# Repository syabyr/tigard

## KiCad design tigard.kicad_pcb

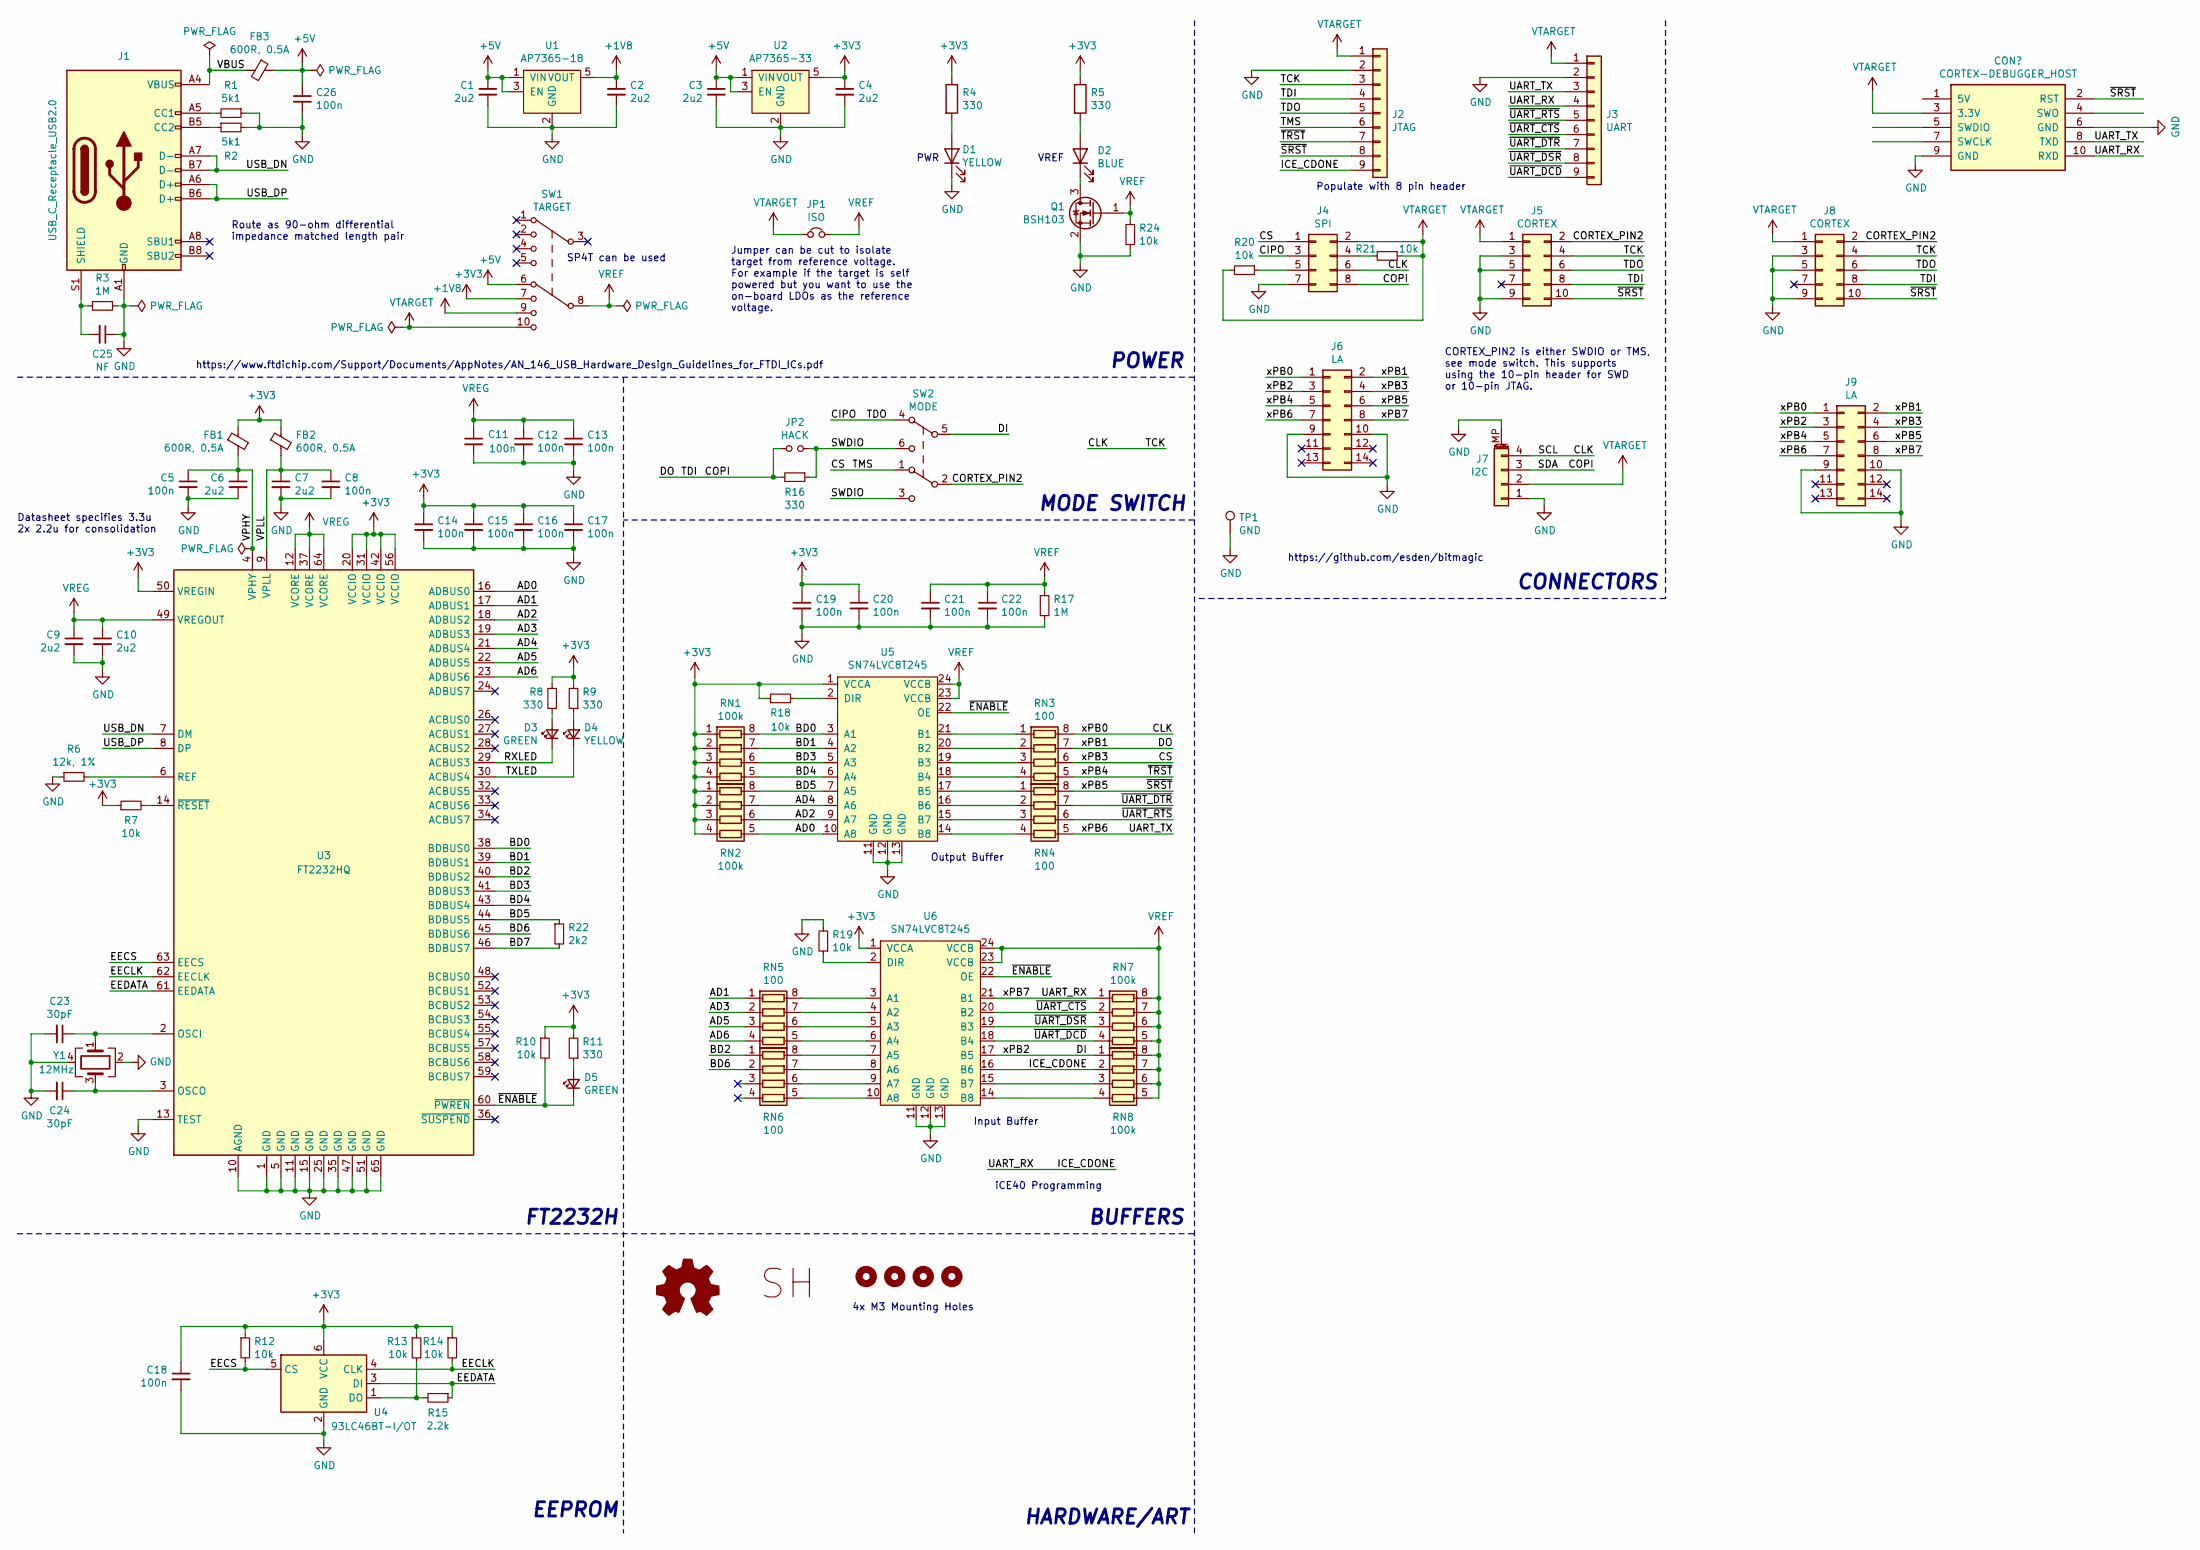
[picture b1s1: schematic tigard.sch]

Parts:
C1, C2, C3, C4, C6, C7, C9, C10: 2u2; C_0402_1005Metric; LCSC C307419
C5, C8, C11, C12, C13, C14, C15, C16, C17, C18, C19, C20, C21, C22, C26: 100n; C_0402_1005Metric; LCSC C100072
C23, C24: 30pF; C_0402_1005Metric; LCSC C159804
C25: NF; C_0402_1005Metric
D1, D4: YELLOW; LED_0603_1608Metric; LCSC C160477
D2: BLUE; LED_0603_1608Metric; LCSC C157738
D3, D5: GREEN; LED_0603_1608Metric; LCSC C12065
FB1, FB2, FB3: 600R, 0.5A; L_0402_1005Metric; LCSC C76886
H1, H2, H3, H4: MountingHole; MountingHole_3.2mm_M3_ISO7380
J1: USB_C_Receptacle_USB2.0; USB_C_Receptacle_HRO_TYPE-C-31-M-12; LCSC C165948
J2: JTAG; PinHeader_1x09_P2.54mm_Vertical; LCSC C358689
J3: UART; PinHeader_1x09_P2.54mm_Vertical; LCSC C492408
J4: SPI; PinHeader_2x04_P2.54mm_Vertical; LCSC C358693
J5: CORTEX; PinHeader_2x05_P1.27mm_Vertical_SMD; LCSC C448647
J6: LA; PinHeader_2x07_P1.27mm_Vertical_SMD
J7: I2C; JST_SH_SM04B-SRSS-TB_1x04-1MP_P1.00mm_Horizontal; LCSC C160404
J8: CORTEX; debugger_2x05_P1.27mm_Vertical; LCSC C448647
J9: LA; PinHeader_2x07_P1.27mm_Vertical
JP1: ISO; SolderJumper-2_P1.3mm_Bridged_RoundedPad1.0x1.5mm
JP2: HACK; SolderJumper-2_P1.3mm_Open_RoundedPad1.0x1.5mm
LOGO1: Logo_Open_Hardware_Small; OSHW-Symbol_4.4x4mm_SilkScreen
LOGO2: Logo_SH; Securing_Hardware_Logo
Q1: BSH103; SOT-23_RoundRect; LCSC C88711
R1, R2: 5k1; R_0402_1005Metric; LCSC C25941
R3, R17: 1M; R_0402_1005Metric; LCSC C26087
R4, R5, R8, R9, R11, R16: 330; R_0402_1005Metric; LCSC C25104
R6: 12k, 1%; R_0402_1005Metric; LCSC C25752
R7, R10, R12, R13, R14, R18, R19, R20, R21, R24: 10k; R_0402_1005Metric; LCSC C301923
R15: 2.2k; R_0402_1005Metric; LCSC C25879
R22: 2k2; R_0402_1005Metric; LCSC C25933
RN1, RN2, RN7, RN8: 100k; R_Array_Convex_4x0402_RoundRect; LCSC C25724
RN3, RN4, RN5, RN6: 100; R_Array_Convex_4x0402_RoundRect; LCSC C48442
SW1: TARGET; SW_ALPS_SSSS224100_DP4T; LCSC C255514
SW2: MODE; SW_CuK_JS202011CQN_DPDT_Straight; LCSC C221663
TP1: GND; TestPoint_Keystone_5000-5004_Miniature; LCSC C238122
U1: AP7365-18; SOT-23-5_RoundRect; LCSC C460402
U2: AP7365-33; SOT-23-5_RoundRect; LCSC C150742
U3: FT2232HQ; QFN-64-1EP_9x9mm_P0.5mm_EP4.35x4.35mm_ThermalVias; LCSC C193662
U4: 93LC46BT-I/OT; SOT-23-6_RoundRect; LCSC C190271
U5, U6: SN74LVC8T245; TSSOP-24_4.4x7.8mm_P0.65mm; LCSC C27643
Y1: 12MHz; Crystal_SMD_3225-4Pin_3.2x2.5mm_RoundRect; LCSC C9002

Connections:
+1V8: C2.1, SW1.9, U1.5 (VOUT)
+3V3: C4.1, C14.1, C15.1, C16.1, C17.1, C18.1, C19.1, C20.1, FB1.1, FB2.1, R4.1, R5.1, R7.1, R8.2, R9.2, R10.1, R11.2, R12.1, R13.1, R14.1, R18.1, RN1.1 (R1.1), RN1.2 (R2.1), RN1.3 (R3.1), RN1.4 (R4.1), RN2.1 (R1.1), RN2.2 (R2.1), RN2.3 (R3.1), RN2.4 (R4.1), SW1.7, U2.5 (VOUT), U3.20 (VCCIO), U3.31 (VCCIO), U3.42 (VCCIO), U3.50 (VREGIN), U3.56 (VCCIO), U4.6 (VCC), U5.1 (VCCA), U6.1 (VCCA)
+5V: C1.1, C3.1, C26.1, FB3.1, SW1.6, U1.1 (VIN), U1.3 (EN), U2.1 (VIN), U2.3 (EN)
/AD0: RN2.5 (R4.2), U3.16 (ADBUS0), U5.10 (A8)
/AD1: RN5.1 (R1.1), U3.17 (ADBUS1)
/AD2: RN2.6 (R3.2), U3.18 (ADBUS2), U5.9 (A7)
/AD3: RN5.2 (R2.1), U3.19 (ADBUS3)
/AD4: RN2.7 (R2.2), U3.21 (ADBUS4), U5.8 (A6)
/AD5: RN5.3 (R3.1), U3.22 (ADBUS5)
/AD6: RN5.4 (R4.1), U3.23 (ADBUS6)
/BD0: RN1.8 (R1.2), U3.38 (BDBUS0), U5.3 (A1)
/BD1: RN1.7 (R2.2), U3.39 (BDBUS1), U5.4 (A2)
/BD2: RN6.1 (R1.1), U3.40 (BDBUS2)
/BD3: RN1.6 (R3.2), U3.41 (BDBUS3), U5.5 (A3)
/BD4: RN1.5 (R4.2), U3.43 (BDBUS4), U5.6 (A4)
/BD5: R22.1, RN2.8 (R1.2), U3.44 (BDBUS5), U5.7 (A5)
/BD6: RN6.2 (R2.1), U3.45 (BDBUS6)
/BD7: R22.2, U3.46 (BDBUS7)
/CIPO: J2.5, J4.3, J5.6, J8.6, SW2.4
/CLK: J2.3, J4.6, J5.4, J6.1, J7.4, J8.4, J9.1, RN3.8 (R1.2)
/COPI: J2.4, J4.8, J5.8, J6.2, J7.3, J8.8, J9.2, JP2.1, R16.2, RN3.7 (R2.2)
/CORTEX_PIN2: J5.2, J8.2, SW2.2
/CS: J2.6, J4.1, J6.4, J9.4, RN3.6 (R3.2), SW2.1
/DI: J6.3, J9.3, RN8.1 (R1.1), SW2.5, U6.17 (B5)
/EECLK: R14.2, U3.62 (EECLK), U4.4 (CLK)
/EECS: R12.2, U3.63 (EECS), U4.5 (CS)
/EEDATA: R15.1, U3.61 (EEDATA), U4.3 (DI)
/ICE_CDONE: J2.9, J3.4, J6.8, J9.8, RN7.1 (R1.1), RN8.2 (R2.1), U6.16 (B6), U6.21 (B1)
/RXLED: D3.1 (K), U3.29 (ACBUS3)
/SWDIO: JP2.2, R16.1, SW2.3, SW2.6
/TXLED: D4.1 (K), U3.30 (ACBUS4)
/UART_TX: J3.3, J6.7, J9.7, RN4.5 (R4.2)
/USB_DN: J1.A7 (D-), J1.B7 (D-), U3.7 (DM)
/USB_DP: J1.A6 (D+), J1.B6 (D+), U3.8 (DP)
/VBUS: FB3.2, J1.A4 (VBUS), J1.A9 (VBUS), J1.B4 (VBUS), J1.B9 (VBUS)
/VPHY: C5.1, C6.1, FB1.2, U3.4 (VPHY)
/VPLL: C7.1, C8.1, FB2.2, U3.9 (VPLL)
/xPB4: J2.7, J6.5, J9.5, RN3.5 (R4.2)
/xPB5: J2.8, J5.10, J6.6, J8.10, J9.6, RN4.8 (R1.2)
/~ENABLE: D5.1 (K), R10.2, U3.60 (~PWREN), U5.22 (OE), U6.22 (OE)
/~UART_CTS: J3.6, RN7.2 (R2.1), U6.20 (B2)
/~UART_DCD: J3.9, RN7.4 (R4.1), U6.18 (B4)
/~UART_DSR: J3.8, RN7.3 (R3.1), U6.19 (B3)
/~UART_DTR: J3.7, RN4.7 (R2.2)
/~UART_RTS: J3.5, RN4.6 (R3.2)
GND: C1.2, C2.2, C3.2, C4.2, C5.2, C6.2, C7.2, C8.2, C9.2, C10.2, C11.2, C12.2, C13.2, C14.2, C15.2, C16.2, C17.2, C18.2, C19.2, C20.2, C21.2, C22.2, C23.2, C24.2, C25.1, C26.2, D1.1 (K), J1.A1 (GND), J1.A12 (GND), J1.B1 (GND), J1.B12 (GND), J2.2, J3.2, J4.7, J5.3, J5.5, J5.9, J6.9, J6.10, J7.1, J7.MP (MountPin), J8.3, J8.5, J8.9, J9.9, J9.10, Q1.2 (S), R1.1, R2.2, R3.1, R6.1, R17.2, R19.2, R24.1, TP1.1, U1.2 (GND), U2.2 (GND), U3.1 (GND), U3.5 (GND), U3.10 (AGND), U3.11 (GND), U3.13 (TEST), U3.15 (GND), U3.25 (GND), U3.35 (GND), U3.47 (GND), U3.51 (GND), U3.65 (GND), U4.2 (GND), U5.11 (GND), U5.12 (GND), U5.13 (GND), U6.11 (GND), U6.12 (GND), U6.13 (GND), Y1.2, Y1.4
unnamed: C23.1, U3.2 (OSCI), Y1.1
unnamed: C24.1, U3.3 (OSCO), Y1.3
unnamed: C25.2, J1.S1 (SHIELD), R3.2
unnamed: D1.2 (A), R4.2
unnamed: D2.1 (K), Q1.3 (D)
unnamed: D2.2 (A), R5.2
unnamed: D3.2 (A), R8.1
unnamed: D4.2 (A), R9.1
unnamed: D5.2 (A), R11.1
unnamed: J1.A5 (CC1), R1.2
unnamed: J1.B5 (CC2), R2.1
unnamed: J4.4, R21.2
unnamed: J4.5, R20.1
unnamed: R6.2, U3.6 (REF)
unnamed: R7.2, U3.14 (~RESET)
unnamed: R13.2, R15.2, U4.1 (DO)
unnamed: R18.2, U5.2 (DIR)
unnamed: R19.1, U6.2 (DIR)
unnamed: RN3.1 (R1.1), U5.21 (B1)
unnamed: RN3.2 (R2.1), U5.20 (B2)
unnamed: RN3.3 (R3.1), U5.19 (B3)
unnamed: RN3.4 (R4.1), U5.18 (B4)
unnamed: RN4.1 (R1.1), U5.17 (B5)
unnamed: RN4.2 (R2.1), U5.16 (B6)
unnamed: RN4.3 (R3.1), U5.15 (B7)
unnamed: RN4.4 (R4.1), U5.14 (B8)
unnamed: RN5.5 (R4.2), U6.6 (A4)
unnamed: RN5.6 (R3.2), U6.5 (A3)
unnamed: RN5.7 (R2.2), U6.4 (A2)
unnamed: RN5.8 (R1.2), U6.3 (A1)
unnamed: RN6.5 (R4.2), U6.10 (A8)
unnamed: RN6.6 (R3.2), U6.9 (A7)
unnamed: RN6.7 (R2.2), U6.8 (A6)
unnamed: RN6.8 (R1.2), U6.7 (A5)
unnamed: RN8.3 (R3.1), U6.15 (B7)
unnamed: RN8.4 (R4.1), U6.14 (B8)
VREF: C21.1, C22.1, JP1.2, Q1.1 (G), R17.1, R24.2, RN7.5 (R4.2), RN7.6 (R3.2), RN7.7 (R2.2), RN7.8 (R1.2), RN8.5 (R4.2), RN8.6 (R3.2), RN8.7 (R2.2), RN8.8 (R1.2), SW1.8, U5.23 (VCCB), U5.24 (VCCB), U6.23 (VCCB), U6.24 (VCCB)
VREG: C9.1, C10.1, C11.1, C12.1, C13.1, U3.12 (VCORE), U3.37 (VCORE), U3.49 (VREGOUT), U3.64 (VCORE)
VTARGET: J2.1, J3.1, J4.2, J5.1, J7.2, J8.1, JP1.1, R20.2, R21.1, SW1.10

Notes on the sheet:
PWR
POWER
VREF
CONNECTORS
FT2232H
EEPROM
Output Buffer
Input Buffer
BUFFERS
MODE SWITCH
Datasheet specifies 3.3u 2x 2.2u for consolidation
HARDWARE/ART
4x M3 Mounting Holes
https://www.ftdichip.com/Support/Documents/AppNotes/AN_146_USB_Hardware_Design_Guidelines_for_FTDI_ICs.pdf
Route as 90-ohm differential impedance matched length pair
SP4T can be used
Jumper can be cut to isolate target from reference voltage. For example if the target is self powered but you want to use the on-board LDOs as the reference voltage.
CORTEX_PIN2 is either SWDIO or TMS, see mode switch. This supports using the 10-pin header for SWD or 10-pin JTAG.
https://github.com/esden/bitmagic
iCE40 Programming
Populate with 8 pin header

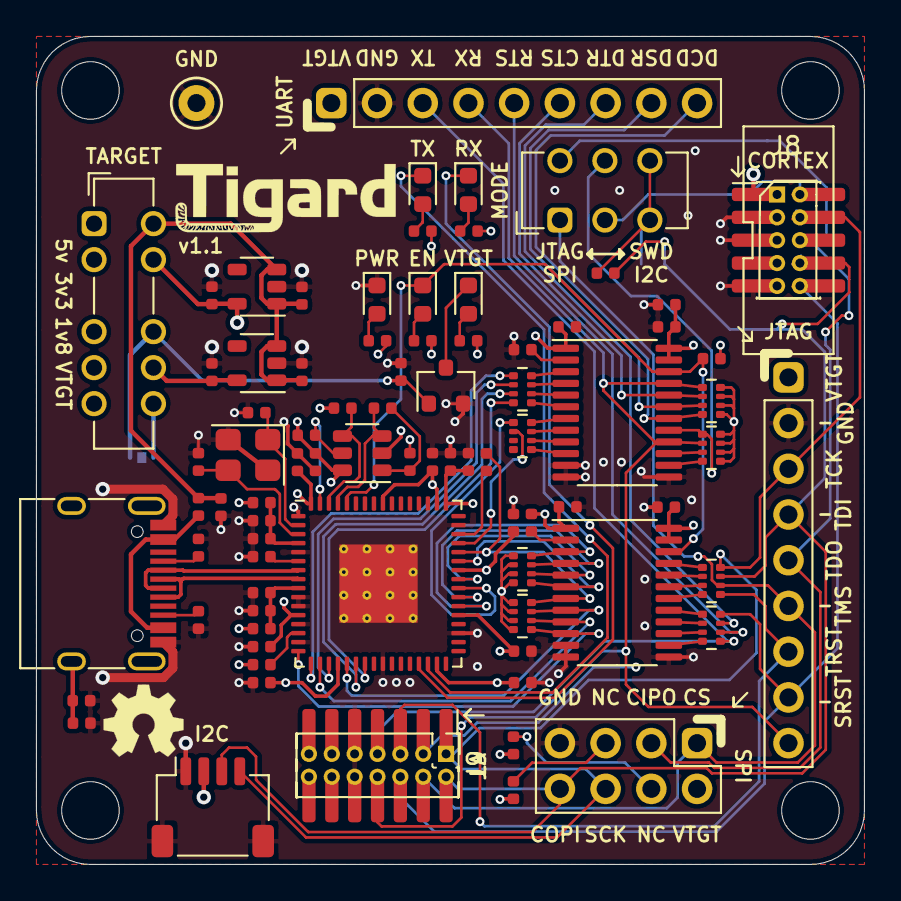
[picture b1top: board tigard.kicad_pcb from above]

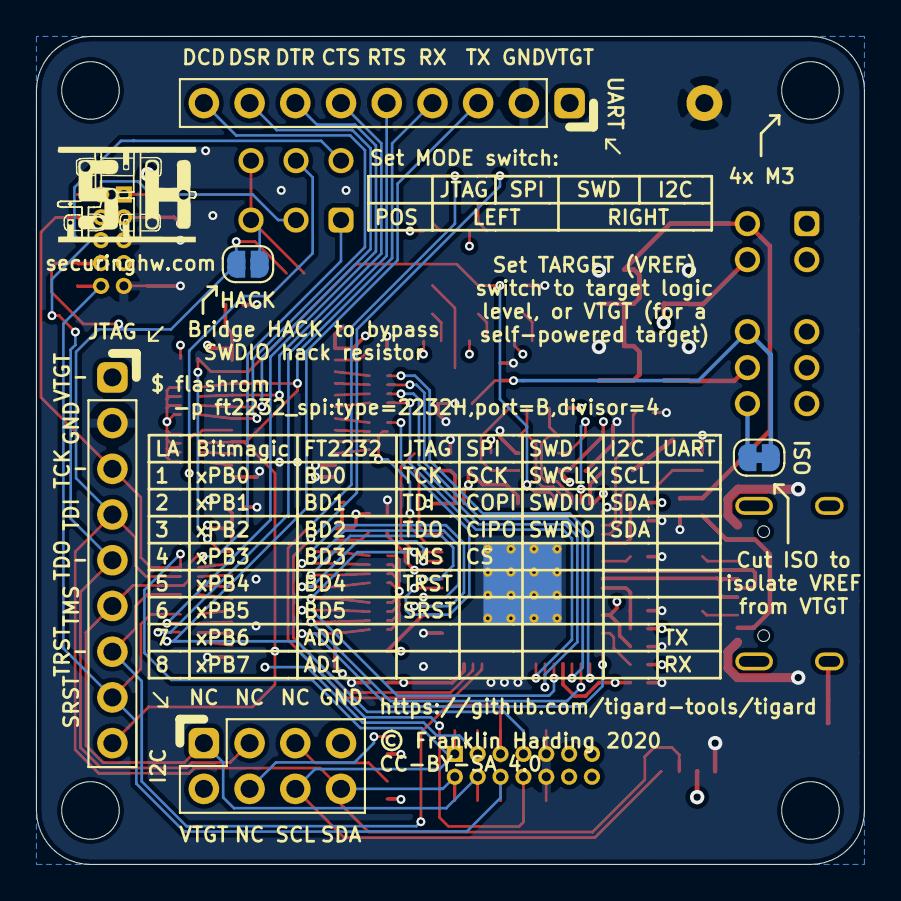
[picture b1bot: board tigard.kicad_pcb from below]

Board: 4 copper layers, 46.0 x 46.0 mm, 93 parts (3 on the bottom side), 85 nets.

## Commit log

2021-04-14 rev1
2021-07-23 v3.1
2021-07-23 v1.3
2021-07-23 v.2.2

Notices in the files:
tigard.kicad_pcb:
Copyright Franklin Harding 2020
Licensed under CC-BY-SA 4.0
© Franklin Harding 2020
CC-BY-SA 4.0
tigard.sch:
Copyright 2020 Franklin Harding
